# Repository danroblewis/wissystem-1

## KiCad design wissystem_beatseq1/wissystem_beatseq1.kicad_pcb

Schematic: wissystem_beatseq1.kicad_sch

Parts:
D1, D4, D6, D8, D10, D12, D14, D16: blue; LED_0603_1608Metric; LCSC C72041
D2, D3, D5, D7, D9, D11, D13, D15, D17, D18: 1N4148WS; D_SOD-323; LCSC C2128
J1: EuroPower16; IDC-Header_2x08_P2.54mm_Vertical
J2, J3: Conn_01x01
J4, J5, J7, J9, J11, J13, J15, J17, J19: Conn_01x03; PinSocket_1x03_P2.54mm_Vertical
J6, J8, J10, J12, J14, J16, J18, J20: Conn_01x05; PinSocket_1x05_P2.54mm_Vertical
J21, J22: Conn_01x02; PinSocket_1x02_P2.54mm_Vertical
JCLK1, JCLK2: Thonkiconn; Jack_3.5mm_QingPu_WQP-PJ398SM_Vertical_CircularHoles
JDEC1, JDEC2, JDEC3, JDEC4, JDEC5, JDEC6, JDEC7, JDEC8, JDEC9, JDEC10, JDEC11, JDEC12, JDEC13, JDEC14, JDEC15, JDEC16, JDEC17, JDEC18, JDEC19, JDEC20, JDEC21: Conn_01x01; PinSocket_1x01_P2.54mm_Vertical
JOUT1: Thonkiconn; Jack_3.5mm_QingPu_WQP-PJ398SM_Vertical_CircularHoles
R2, R3: 150k; R_0402_1005Metric; LCSC C25755
R4, R5, R6, R7, R8, R9, R10, R11: 4.7k; R_0402_1005Metric; LCSC C25900
R12, R14: 100k; R_0402_1005Metric; LCSC C25741
R13: 1k; R_0603_1608Metric; LCSC C21190
SW1, SW2, SW3, SW4, SW5, SW6, SW7, SW8, SW41, SW42, SW43, SW44, SW45, SW46, SW47, SW48: PUSHBTN_DPDT_LATCH; SMD switch 6pin; lcsc C2941005
U1, U3, U4: TL072CDT; SOIC-8_3.9x4.9mm_P1.27mm; LCSC C6961
U2, U12: CD4017BM; SOP-16_4.4x10.4mm_P1.27mm; lcsc C356694

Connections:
+5V: J1.11 (+5V), J1.12 (+5V), J6.5, J8.5, J10.5, J12.5, J14.5, J16.5, J18.5, J20.5, R2.1, SW1.5 (A), SW2.5 (A), SW3.5 (A), SW4.5 (A), SW5.5 (A), SW6.5 (A), SW7.5 (A), SW8.5 (A), U2.16 (VDD), U12.16 (VDD)
CV: J1.13 (CV), J1.14 (CV)
GATE: J1.15 (GATE), J1.16 (GATE)
GND: J1.3 (GND), J1.4 (GND), J1.5 (GND), J1.6 (GND), J1.7 (GND), J1.8 (GND), J6.1, J8.1, J10.1, J12.1, J14.1, J16.1, J18.1, J20.1, JCLK1.S (GND), JCLK2.S (GND), JDEC20.1, JDEC21.1, JOUT1.S (GND), R3.2, R4.2, R5.2, R6.2, R7.2, R8.2, R9.2, R10.2, R11.2, R14.2, U2.8 (VSS), U2.13 (CKEN), U12.8 (VSS), U12.13 (CKEN)
unnamed: D1.2 (A), SW1.6 (B)
unnamed: D1.1 (K), R4.1
unnamed: D2.2 (A), SW1.3 (B)
unnamed: D3.2 (A), SW2.3 (B)
unnamed: D4.2 (A), SW2.6 (B)
unnamed: D4.1 (K), R5.1
unnamed: D5.2 (A), SW3.3 (B)
unnamed: D6.2 (A), SW3.6 (B)
unnamed: D6.1 (K), R6.1
unnamed: D7.2 (A), SW4.3 (B)
unnamed: D8.2 (A), SW4.6 (B)
unnamed: D8.1 (K), R7.1
unnamed: D9.2 (A), SW5.3 (B)
unnamed: D10.2 (A), SW5.6 (B)
unnamed: D10.1 (K), R8.1
unnamed: D11.2 (A), SW6.3 (B)
unnamed: D2.1 (K), D3.1 (K), D5.1 (K), D7.1 (K), D9.1 (K), D11.1 (K), D13.1 (K), D15.1 (K), U3.3 (+)
unnamed: D12.2 (A), SW6.6 (B)
unnamed: D12.1 (K), R9.1
unnamed: D13.2 (A), SW7.3 (B)
unnamed: D14.2 (A), SW7.6 (B)
unnamed: D14.1 (K), R10.1
unnamed: D15.2 (A), SW8.3 (B)
unnamed: D16.2 (A), SW8.6 (B)
unnamed: D16.1 (K), R11.1
unnamed: D17.2 (A), D18.2 (A), R12.2
unnamed: D18.1 (K), R14.1, U3.5 (+)
unnamed: J2.1, U12.14 (CLK)
unnamed: J4.3, JDEC9.1, JDEC10.1, JDEC11.1, JDEC12.1, JDEC13.1, JDEC14.1, JDEC15.1, JDEC16.1
unnamed: J5.1, SW41.1 (A)
unnamed: J5.2, SW41.2 (A)
unnamed: J5.3, SW41.3 (B)
unnamed: J6.2, SW41.4 (A)
unnamed: J6.3, SW41.5 (A)
unnamed: J6.4, SW41.6 (B)
unnamed: J7.1, SW42.1 (A)
unnamed: J7.2, SW42.2 (A)
unnamed: J7.3, SW42.3 (B)
unnamed: J8.2, SW42.4 (A)
unnamed: J8.3, SW42.5 (A)
unnamed: J8.4, SW42.6 (B)
unnamed: J9.1, SW44.1 (A)
unnamed: J9.2, SW44.2 (A)
unnamed: J9.3, SW44.3 (B)
unnamed: J10.2, SW44.4 (A)
unnamed: J10.3, SW44.5 (A)
unnamed: J10.4, SW44.6 (B)
unnamed: J11.1, SW43.1 (A)
unnamed: J11.2, SW43.2 (A)
unnamed: J11.3, SW43.3 (B)
unnamed: J12.2, SW43.4 (A)
unnamed: J12.3, SW43.5 (A)
unnamed: J12.4, SW43.6 (B)
unnamed: J13.1, SW45.1 (A)
unnamed: J13.2, SW45.2 (A)
unnamed: J13.3, SW45.3 (B)
unnamed: J14.2, SW45.4 (A)
unnamed: J14.3, SW45.5 (A)
unnamed: J14.4, SW45.6 (B)
unnamed: J15.1, SW46.1 (A)
unnamed: J15.2, SW46.2 (A)
unnamed: J15.3, SW46.3 (B)
unnamed: J16.2, SW46.4 (A)
unnamed: J16.3, SW46.5 (A)
unnamed: J16.4, SW46.6 (B)
unnamed: J17.1, SW47.1 (A)
unnamed: J17.2, SW47.2 (A)
unnamed: J17.3, SW47.3 (B)
unnamed: J18.2, SW47.4 (A)
unnamed: J18.3, SW47.5 (A)
unnamed: J18.4, SW47.6 (B)
unnamed: J19.1, SW48.1 (A)
unnamed: J19.2, SW48.2 (A)
unnamed: J19.3, SW48.3 (B)
unnamed: J20.2, SW48.4 (A)
unnamed: J20.3, SW48.5 (A)
unnamed: J20.4, SW48.6 (B)
unnamed: J21.1, U4.2 (-)
unnamed: J21.2, U4.3 (+)
unnamed: J22.1, U4.6 (-)
unnamed: J22.2, U4.5 (+)
unnamed: JDEC1.1, U12.2 (Q1)
unnamed: JDEC2.1, U12.4 (Q2)
unnamed: JDEC3.1, U12.7 (Q3)
unnamed: JDEC4.1, U12.10 (Q4)
unnamed: JDEC5.1, U12.1 (Q5)
unnamed: JDEC6.1, U12.5 (Q6)
unnamed: JDEC7.1, U12.6 (Q7)
unnamed: JDEC8.1, U12.3 (Q0)
unnamed: JDEC17.1, U1.5 (+)
unnamed: JDEC18.1, U4.1
unnamed: JDEC19.1, U4.7
unnamed: JOUT1.T, R13.2
unnamed: R2.2, R3.1
unnamed: R12.1, U3.1
unnamed: JCLK1.T, U1.3 (+)
unnamed: JCLK2.T, U1.6 (-), U1.7
unnamed: SW1.2 (A), U2.3 (Q0)
unnamed: SW2.2 (A), U2.2 (Q1)
unnamed: SW3.2 (A), U2.4 (Q2)
unnamed: SW4.2 (A), U2.7 (Q3)
unnamed: SW5.2 (A), U2.10 (Q4)
unnamed: SW6.2 (A), U2.1 (Q5)
unnamed: SW7.2 (A), U2.5 (Q6)
unnamed: SW8.2 (A), U2.6 (Q7)
unnamed: U2.9 (Q8), U2.15 (Reset)
unnamed: R13.1, U3.6 (-), U3.7
unnamed: U12.9 (Q8), U12.15 (Reset)
clock: D17.1 (K), J3.1, J4.1, U1.1, U2.14 (CLK)
ref: J4.2, U1.2 (-), U3.2 (-)

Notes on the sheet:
https://www.falstad.com/circuit/circuitjs.html?ctz=CQAgjCAMB0l3BWEA2aAWB8CcBmSy0AOBBAdkJE0pDR0oFMBaMMAKACVw00UetleUEACYQhSCOhJhUkDmhg0YBFmHIEOBISylcUBcIQcuPMMIr9w5oaPGTps+auRYskQmBeFSwpTxhmRpyKpqoglmBhErbRsjJIaNCkZjiE2uKpaC76gcYhIggCloYC0WKxDkgI6DrkybTkwmCpOYasAM4mgr4SBEISAGYAhgA27fQdXWYUPVYUEhDDYx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

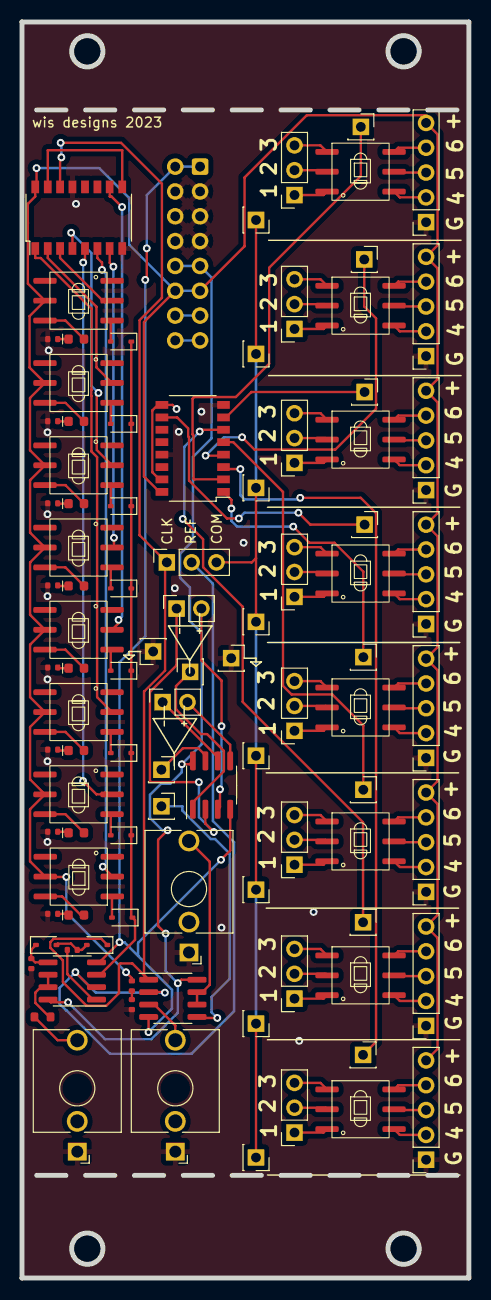
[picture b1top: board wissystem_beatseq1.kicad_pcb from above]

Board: 2 copper layers, 45.7 x 128.5 mm, 96 parts (1 on the bottom side), 115 nets.

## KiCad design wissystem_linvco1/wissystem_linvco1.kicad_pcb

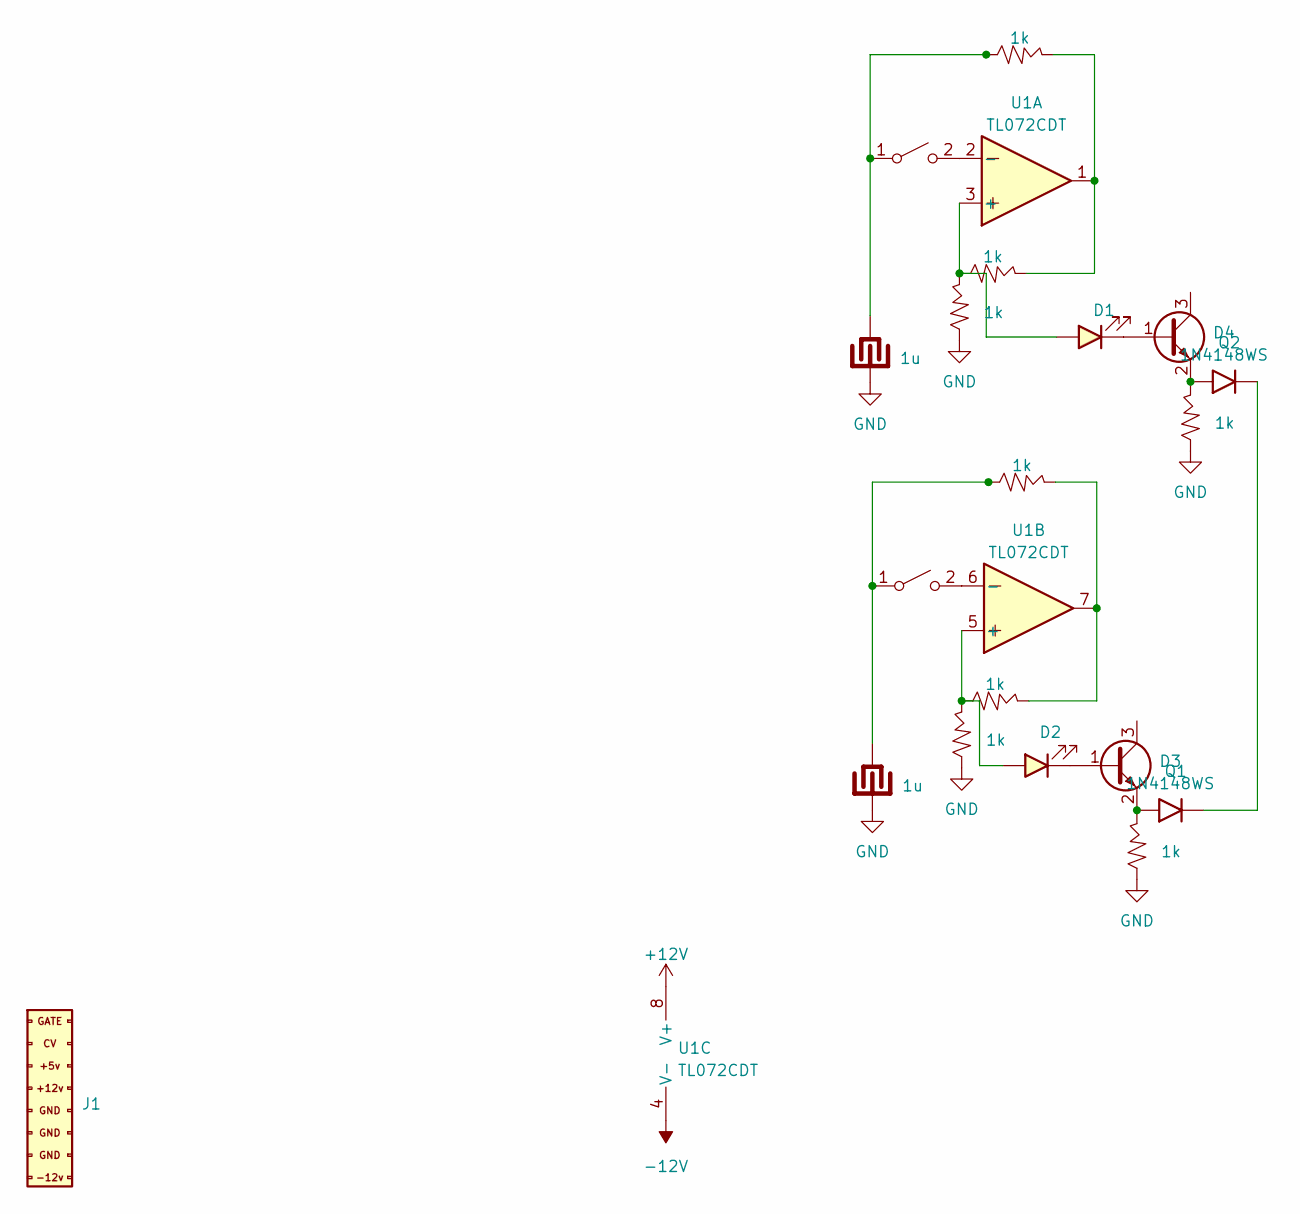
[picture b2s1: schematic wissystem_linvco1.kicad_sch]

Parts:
C1, C2: 1u; C_0805_2012Metric; LCSC C28323
D1, D2: white; LED_0805_2012Metric; LCSC C34499
D3, D4: 1N4148WS; D_SOD-323; LCSC C2128
J1: EuroPower16; IDC-Header_2x08_P2.54mm_Vertical_SMD; lcsc C383608
Q1, Q2: NPN S8050 J3Y; SOT-23; LCSC C2146
R1, R2, R3, R4, R5, R6, R7, R8: 1k; R_0603_1608Metric; LCSC C21190
SW1, SW2: SW_SPST; SW_SPST_PTS645; lcsc C294565
U1: TL072CDT; SOIC-8_3.9x4.9mm_P1.27mm; LCSC C6961

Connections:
+5V: J1.11 (+5V), J1.12 (+5V)
+12V: J1.9 (+12V), J1.10 (+12V), U1.8 (V+)
-12V: J1.1 (-12V), J1.2 (-12V), U1.4 (V-)
CV: J1.13 (CV), J1.14 (CV)
GATE: J1.15 (GATE), J1.16 (GATE)
GND: C1.2, C2.2, J1.3 (GND), J1.4 (GND), J1.5 (GND), J1.6 (GND), J1.7 (GND), J1.8 (GND), R1.1, R3.1, R7.1, R8.1
unnamed: D1.2 (A), R2.1, R3.2, U1.3 (+)
unnamed: D1.1 (K), Q2.1 (B)
unnamed: D2.2 (A), R1.2, R4.1, U1.5 (+)
unnamed: D2.1 (K), Q1.1 (B)
unnamed: D3.2 (A), Q1.2 (E), R7.2
unnamed: D3.1 (K), D4.1 (K)
unnamed: D4.2 (A), Q2.2 (E), R8.2
unnamed: R2.2, R5.2, U1.1
unnamed: R4.2, R6.2, U1.7
unnamed: C2.1, R6.1, SW1.1 (A)
unnamed: SW1.2 (B), U1.6 (-)
unnamed: C1.1, R5.1, SW2.1 (A)
unnamed: SW2.2 (B), U1.2 (-)

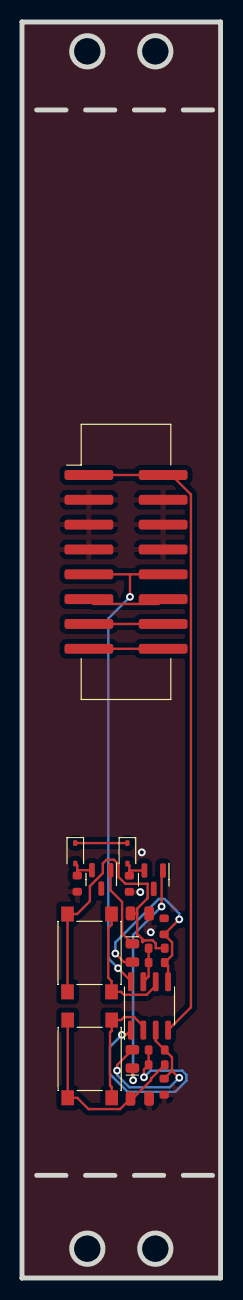
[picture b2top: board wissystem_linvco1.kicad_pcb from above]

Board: 2 copper layers, 20.3 x 128.5 mm, 20 parts (0 on the bottom side), 19 nets.

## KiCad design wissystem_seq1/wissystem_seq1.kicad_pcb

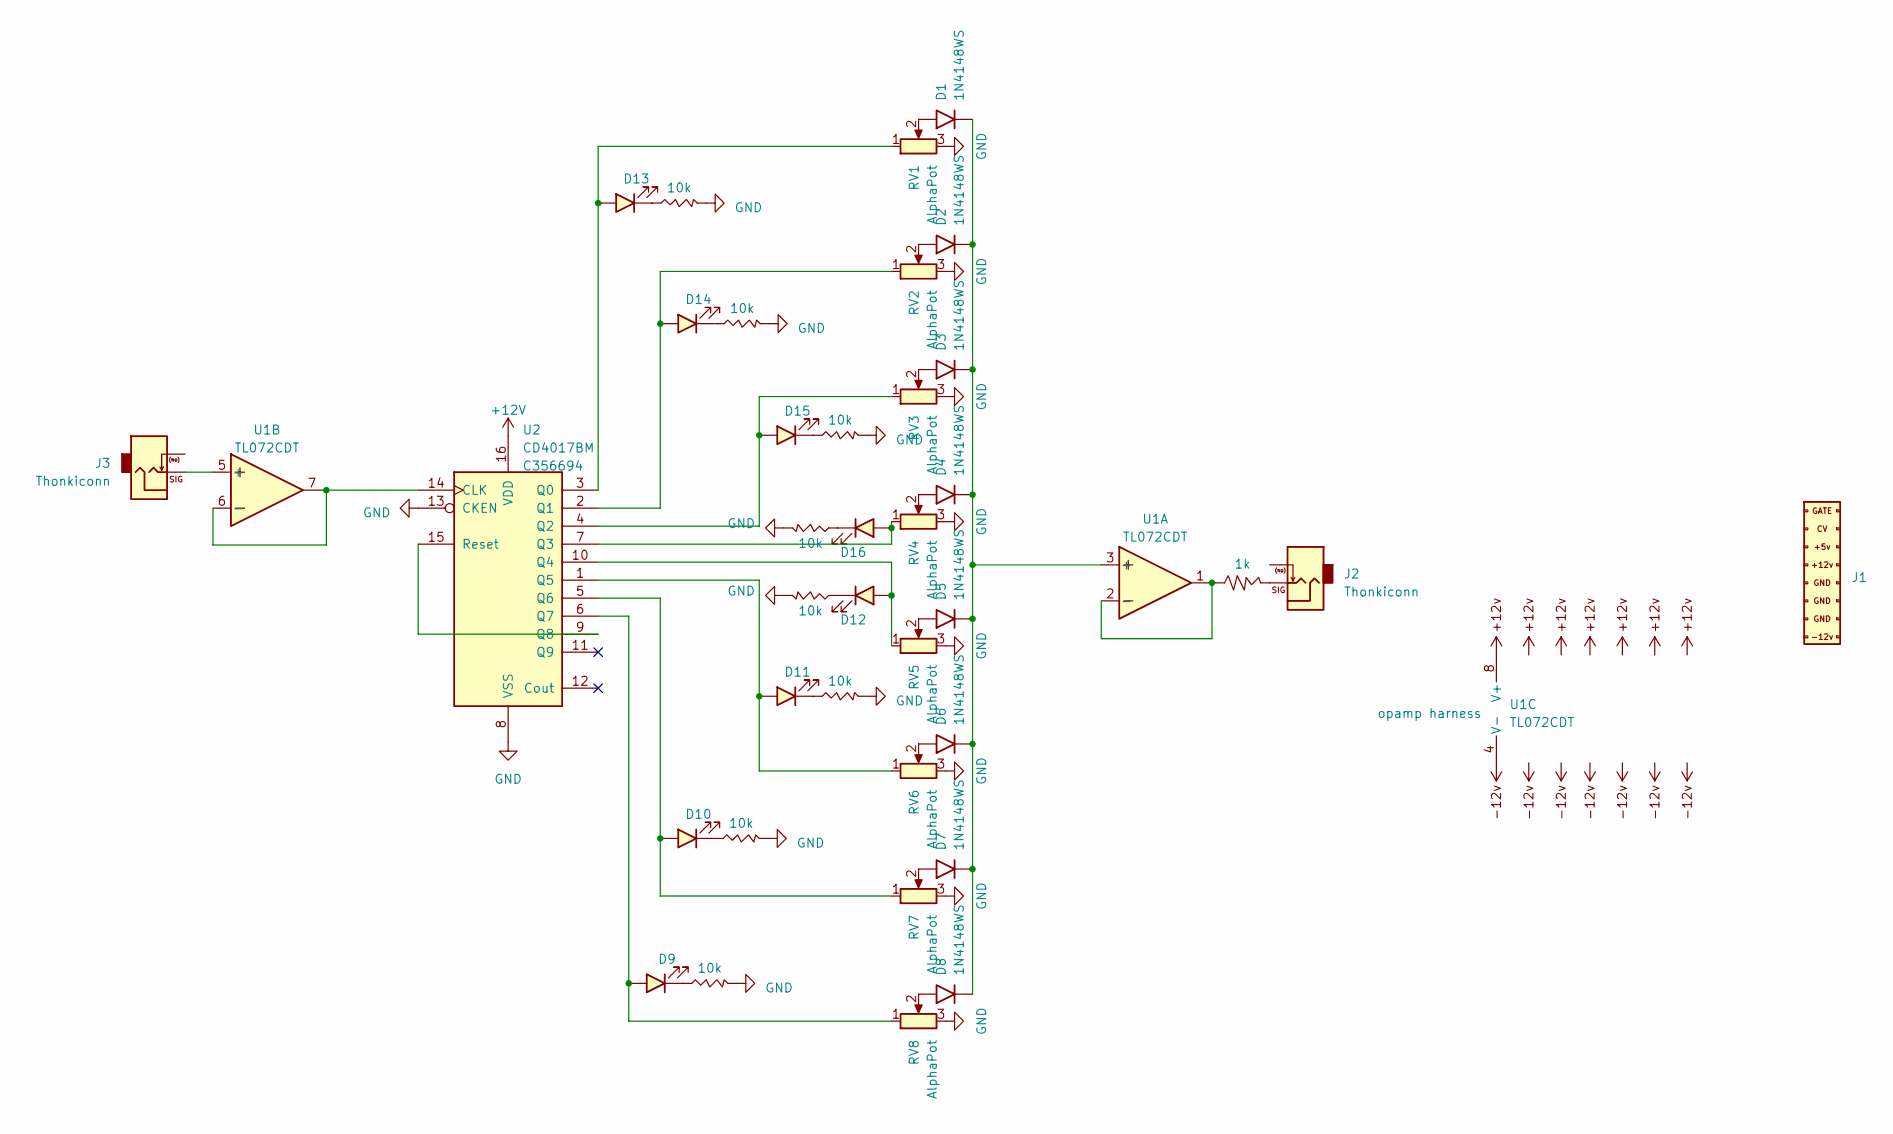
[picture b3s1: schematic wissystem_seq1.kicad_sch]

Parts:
D1, D2, D3, D4, D5, D6, D7, D8: 1N4148WS; D_SOD-323; LCSC C2128
D9, D10, D11, D12, D13, D14, D15, D16: blue; LED_0603_1608Metric; LCSC C72041
J1: EuroPower16; IDC-Header_2x08_P2.54mm_Vertical_SMD; lcsc C383608
J2, J3: Thonkiconn; Jack_3.5mm_QingPu_WQP-PJ398SM_Vertical_CircularHoles
R1: 1k; R_0603_1608Metric; LCSC C21190
R2, R3, R4, R5, R6, R7, R8, R9: 10k; R_0402_1005Metric; LCSC C25744
RV1, RV2, RV3, RV4, RV5, RV6, RV7, RV8: AlphaPot; Potentiometer_Alpha_RD901F-40-00D_Single_Vertical
U1: TL072CDT; SOIC-8_3.9x4.9mm_P1.27mm; LCSC C6961
U2: CD4017BM; SOP-16_4.4x10.4mm_P1.27mm; lcsc C356694

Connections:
+5V: J1.11 (+5V), J1.12 (+5V)
CV: J1.13 (CV), J1.14 (CV)
GATE: J1.15 (GATE), J1.16 (GATE)
GND: J1.3 (GND), J1.4 (GND), J1.5 (GND), J1.6 (GND), J1.7 (GND), J1.8 (GND), J2.S (GND), J3.S (GND), R2.2, R3.2, R4.2, R5.2, R6.2, R7.2, R8.2, R9.2, RV1.3, RV2.3, RV3.3, RV4.3, RV5.3, RV6.3, RV7.3, RV8.3, U2.8 (VSS), U2.13 (CKEN)
unnamed: D1.2 (A), RV1.2
unnamed: D1.1 (K), D2.1 (K), D3.1 (K), D4.1 (K), D5.1 (K), D6.1 (K), D7.1 (K), D8.1 (K), U1.3 (+)
unnamed: D2.2 (A), RV2.2
unnamed: D3.2 (A), RV3.2
unnamed: D4.2 (A), RV4.2
unnamed: D5.2 (A), RV5.2
unnamed: D6.2 (A), RV6.2
unnamed: D7.2 (A), RV7.2
unnamed: D8.2 (A), RV8.2
unnamed: D9.2 (A), RV8.1, U2.6 (Q7)
unnamed: D9.1 (K), R2.1
unnamed: D10.2 (A), RV7.1, U2.5 (Q6)
unnamed: D10.1 (K), R3.1
unnamed: D11.2 (A), RV6.1, U2.1 (Q5)
unnamed: D11.1 (K), R4.1
unnamed: D12.2 (A), RV5.1, U2.10 (Q4)
unnamed: D12.1 (K), R5.1
unnamed: D13.2 (A), RV1.1, U2.3 (Q0)
unnamed: D13.1 (K), R6.1
unnamed: D14.2 (A), RV2.1, U2.2 (Q1)
unnamed: D14.1 (K), R7.1
unnamed: D15.2 (A), RV3.1, U2.4 (Q2)
unnamed: D15.1 (K), R8.1
unnamed: D16.2 (A), RV4.1, U2.7 (Q3)
unnamed: D16.1 (K), R9.1
unnamed: J2.T, R1.2
unnamed: R1.1, U1.1, U1.2 (-)
unnamed: J3.T, U1.5 (+)
unnamed: U1.6 (-), U1.7, U2.14 (CLK)
unnamed: U2.9 (Q8), U2.15 (Reset)

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
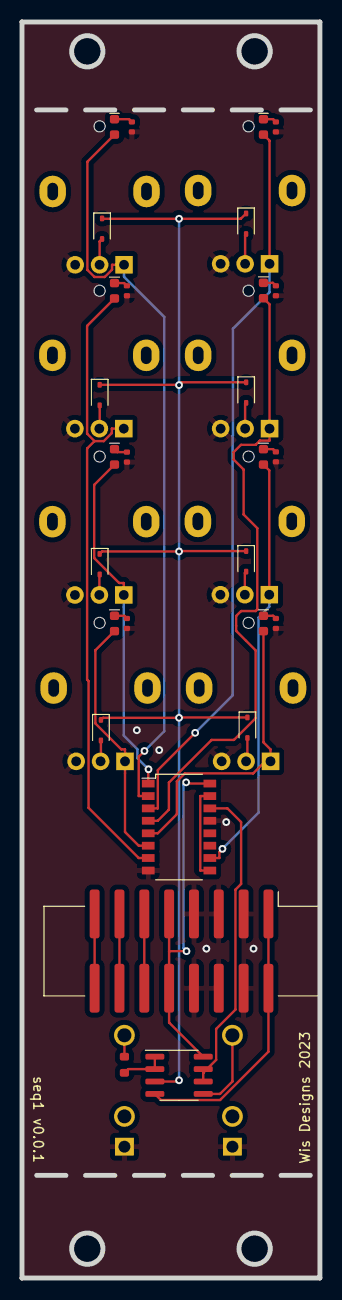
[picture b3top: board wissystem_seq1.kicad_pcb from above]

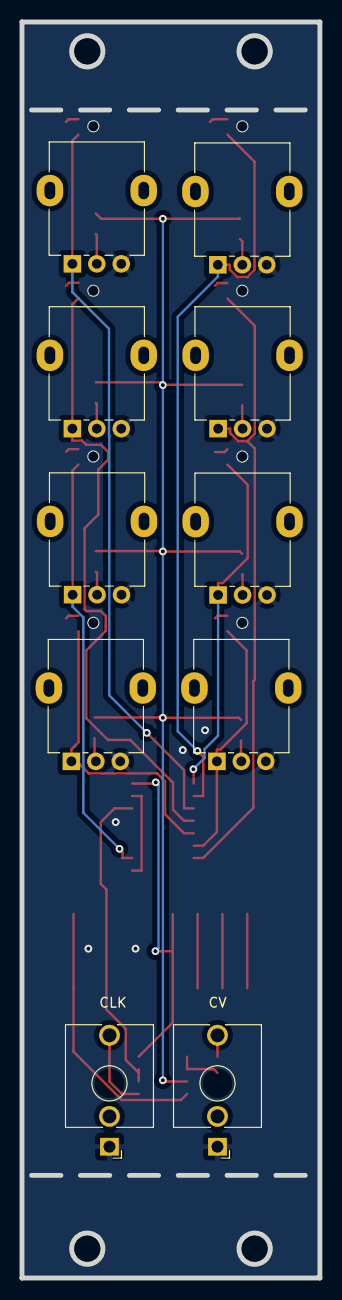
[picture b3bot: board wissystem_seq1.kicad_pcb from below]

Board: 2 copper layers, 30.5 x 128.5 mm, 38 parts (10 on the bottom side), 36 nets.

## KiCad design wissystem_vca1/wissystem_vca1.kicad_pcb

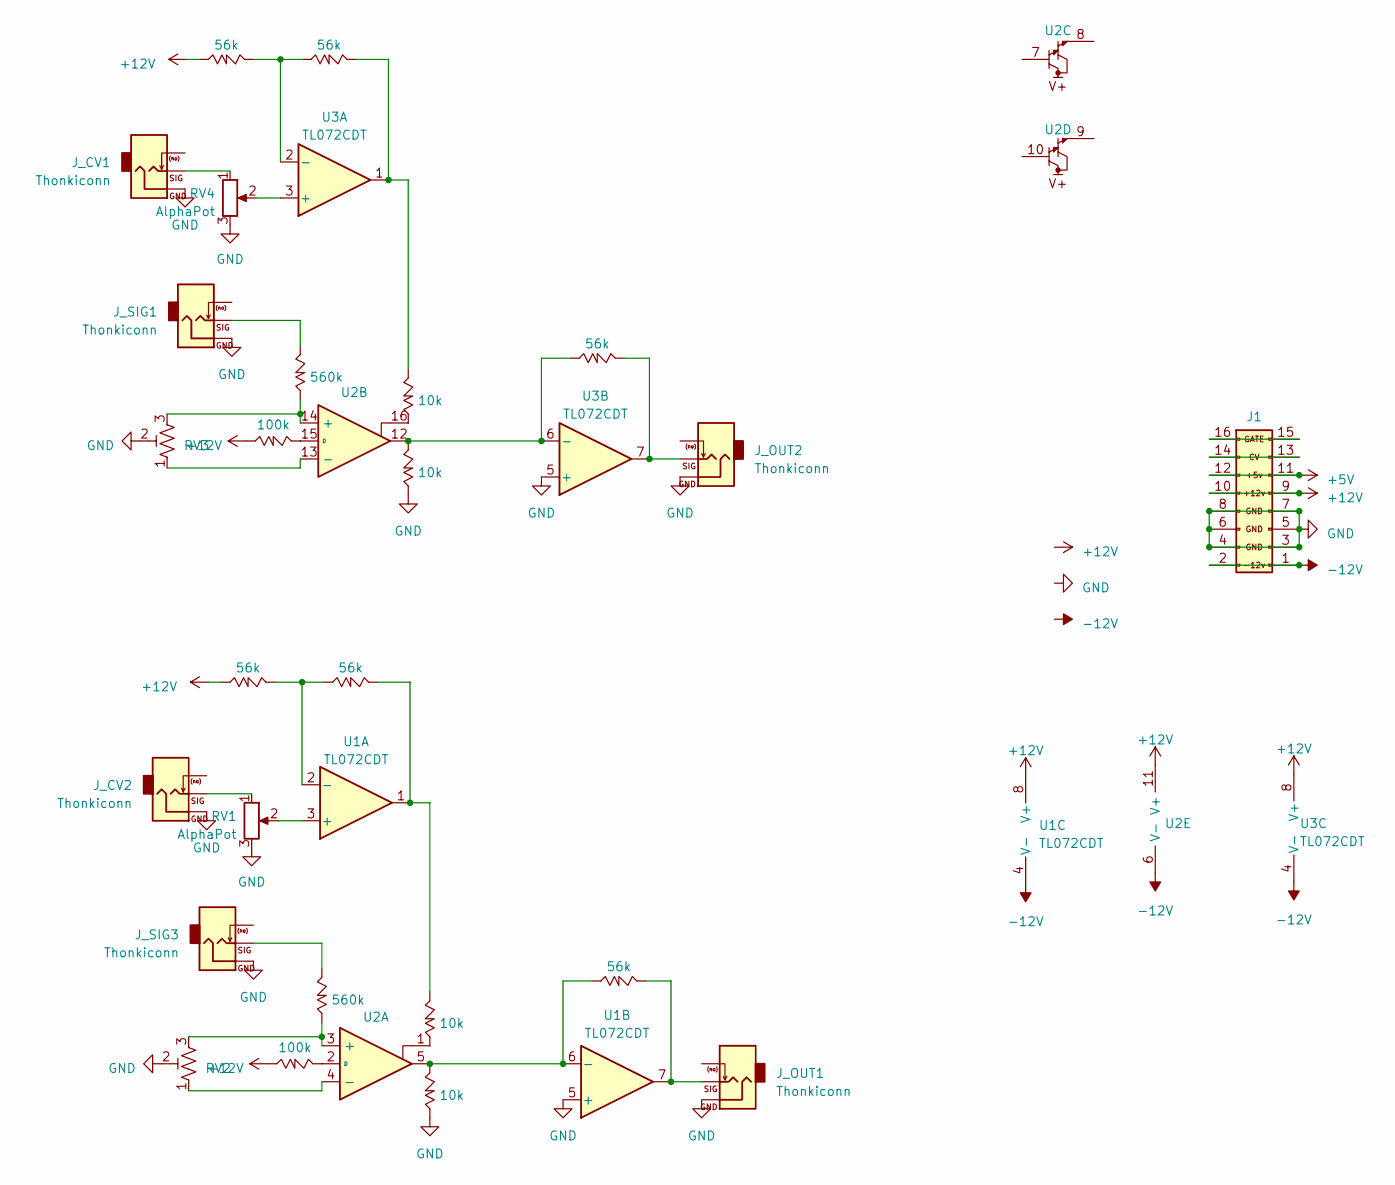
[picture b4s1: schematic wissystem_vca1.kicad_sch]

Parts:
J1: EuroPower16; IDC-Header_2x08_P2.54mm_Vertical_SMD; lcsc C383608
J_CV1, J_CV2: Thonkiconn; Jack_3.5mm_QingPu_WQP-PJ398SM_Vertical_CircularHoles
J_OUT1, J_OUT2: Thonkiconn; Jack_3.5mm_QingPu_WQP-PJ398SM_Vertical_CircularHoles
J_SIG1, J_SIG3: Thonkiconn; Jack_3.5mm_QingPu_WQP-PJ398SM_Vertical_CircularHoles
R1, R2, R7, R8, R11, R14: 56k; R_0402_1005Metric; LCSC C25796
R3, R9: 100k; R_0402_1005Metric; LCSC C25741
R4, R10: 560k; R_0603_1608Metric; LCSC C23203
R5, R6, R12, R13: 10k; R_0402_1005Metric; LCSC C25744
RV1, RV4: AlphaPot; Potentiometer_Alpha_RD901F-40-00D_Single_Vertical
RV2, RV3: R_Potentiometer_Trim_US; Potentiometer_Bourns_TC33X_Vertical; lcsc C128545
U1, U3: TL072CDT; SOIC-8_3.9x4.9mm_P1.27mm; LCSC C6961
U2: XL13700; SOP-16_3.9x9.9mm_P1.27mm; LCSC C521166

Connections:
+5V: J1.11 (+5v_R), J1.12 (+5v_L)
+12V: J1.9 (+12V_R), J1.10 (+12V_L), R2.1, R3.1, R8.1, R9.1, U1.8 (V+), U2.11 (V+), U3.8 (V+)
-12V: J1.1 (-12v_R), J1.2 (-12v_L), U1.4 (V-), U2.6 (V-), U3.4 (V-)
GND: J1.3 (GND), J1.4 (GND), J1.5 (GND_R3), J1.6 (GND_L3), J1.7 (GND_R2), J1.8 (GND_L2), J_CV1.S, J_CV2.S, J_OUT1.S, J_OUT2.S, J_SIG1.S, J_SIG3.S, R6.1, R13.1, RV1.3, RV2.2, RV3.2, RV4.3, U1.5 (+), U3.5 (+)
unnamed: J1.13 (CV_R), J1.14 (CV_L)
unnamed: J1.15 (GATE_R), J1.16 (GATE_L)
unnamed: J_CV1.T, RV4.1
unnamed: J_CV2.T, RV1.1
unnamed: J_OUT1.T, R7.2, U1.7
unnamed: J_OUT2.T, R14.2, U3.7
unnamed: J_SIG1.T, R10.2
unnamed: J_SIG3.T, R4.2
unnamed: R1.2, R5.2, U1.1
unnamed: R5.1, U2.1
unnamed: R11.2, R12.2, U3.1
unnamed: R12.1, U2.16
unnamed: RV1.2, U1.3 (+)
unnamed: R1.1, R2.2, U1.2 (-)
unnamed: R6.2, R7.1, U1.6 (-), U2.5
unnamed: R4.1, RV2.3, U2.3 (+)
unnamed: RV2.1, U2.4 (-)
unnamed: R3.2, U2.2 (D)
unnamed: R10.1, RV3.3, U2.14 (+)
unnamed: RV3.1, U2.13 (-)
unnamed: R9.2, U2.15 (D)
unnamed: RV4.2, U3.3 (+)
unnamed: R8.2, R11.1, U3.2 (-)
unnamed: R13.2, R14.1, U2.12, U3.6 (-)

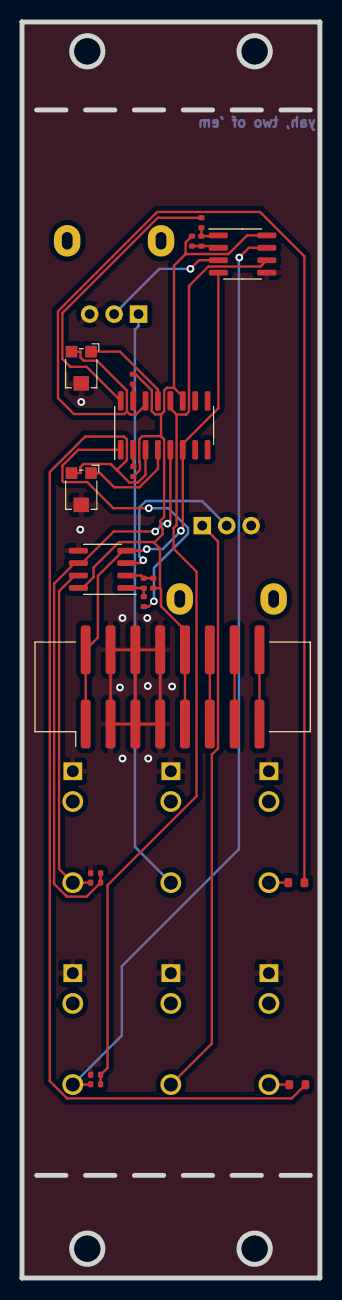
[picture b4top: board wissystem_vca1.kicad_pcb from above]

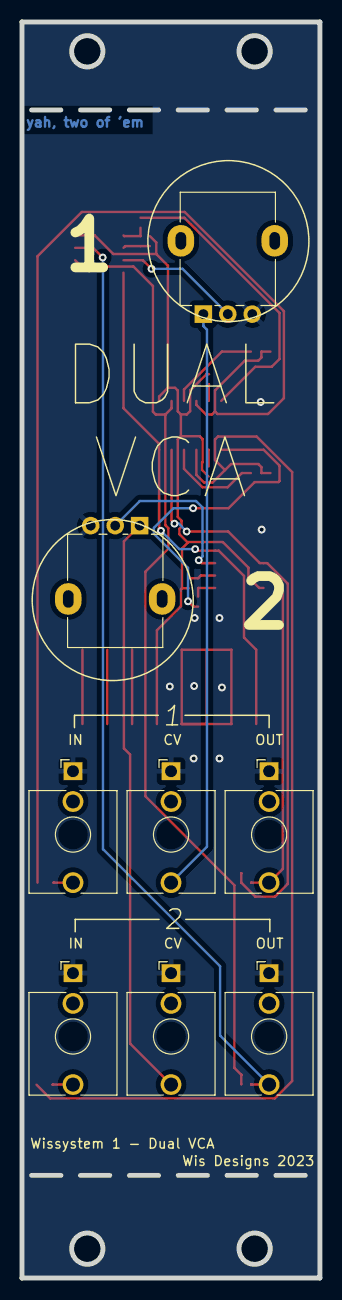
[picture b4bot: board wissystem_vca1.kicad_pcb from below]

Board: 2 copper layers, 30.5 x 128.5 mm, 28 parts (8 on the bottom side), 28 nets.

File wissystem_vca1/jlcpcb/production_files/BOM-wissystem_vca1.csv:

Comment,Designator,Footprint,LCSC
R_Potentiometer_Trim_US,"RV2,RV3",Potentiometer_Bourns_TC33X_Vertical,C128545
560k,"R10,R4",R_0603_1608Metric,C23203
100k,"R3,R9",R_0402_1005Metric,C25741
10k,"R12,R13,R5,R6",R_0402_1005Metric,C25744
56k,"R1,R11,R14,R2,R7,R8",R_0402_1005Metric,C25796
EuroPower16,J1,IDC-Header_2x08_P2.54mm_Vertical_SMD,C383608
XL13700,U2,SOP-16_3.9x9.9mm_P1.27mm,C521166
TL072CDT,"U1,U3",SOIC-8_3.9x4.9mm_P1.27mm,C6961
AlphaPot,RV4,Potentiometer_Alpha_RD901F-40-00D_Single_Vertical,
AlphaPot,RV1,Potentiometer_Alpha_RD901F-40-00D_Single_Vertical,

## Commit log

2023-04-20 asdf
2023-04-27 initial work on wyw2
2023-05-08 update packages for wisseq
2023-05-08 made protoboard for the latching switches
